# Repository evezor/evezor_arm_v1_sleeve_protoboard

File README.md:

# evezor_arm_v1_sleeve_protoboard

This board was intended to sit at the elbow of the robotic arm and serve as a prototyping area to create new ciruits. It has a 10 pin IDE port to connect gpio to the sleeve controller board, but this avenue was abandoned as there were many issues keeping things simple.

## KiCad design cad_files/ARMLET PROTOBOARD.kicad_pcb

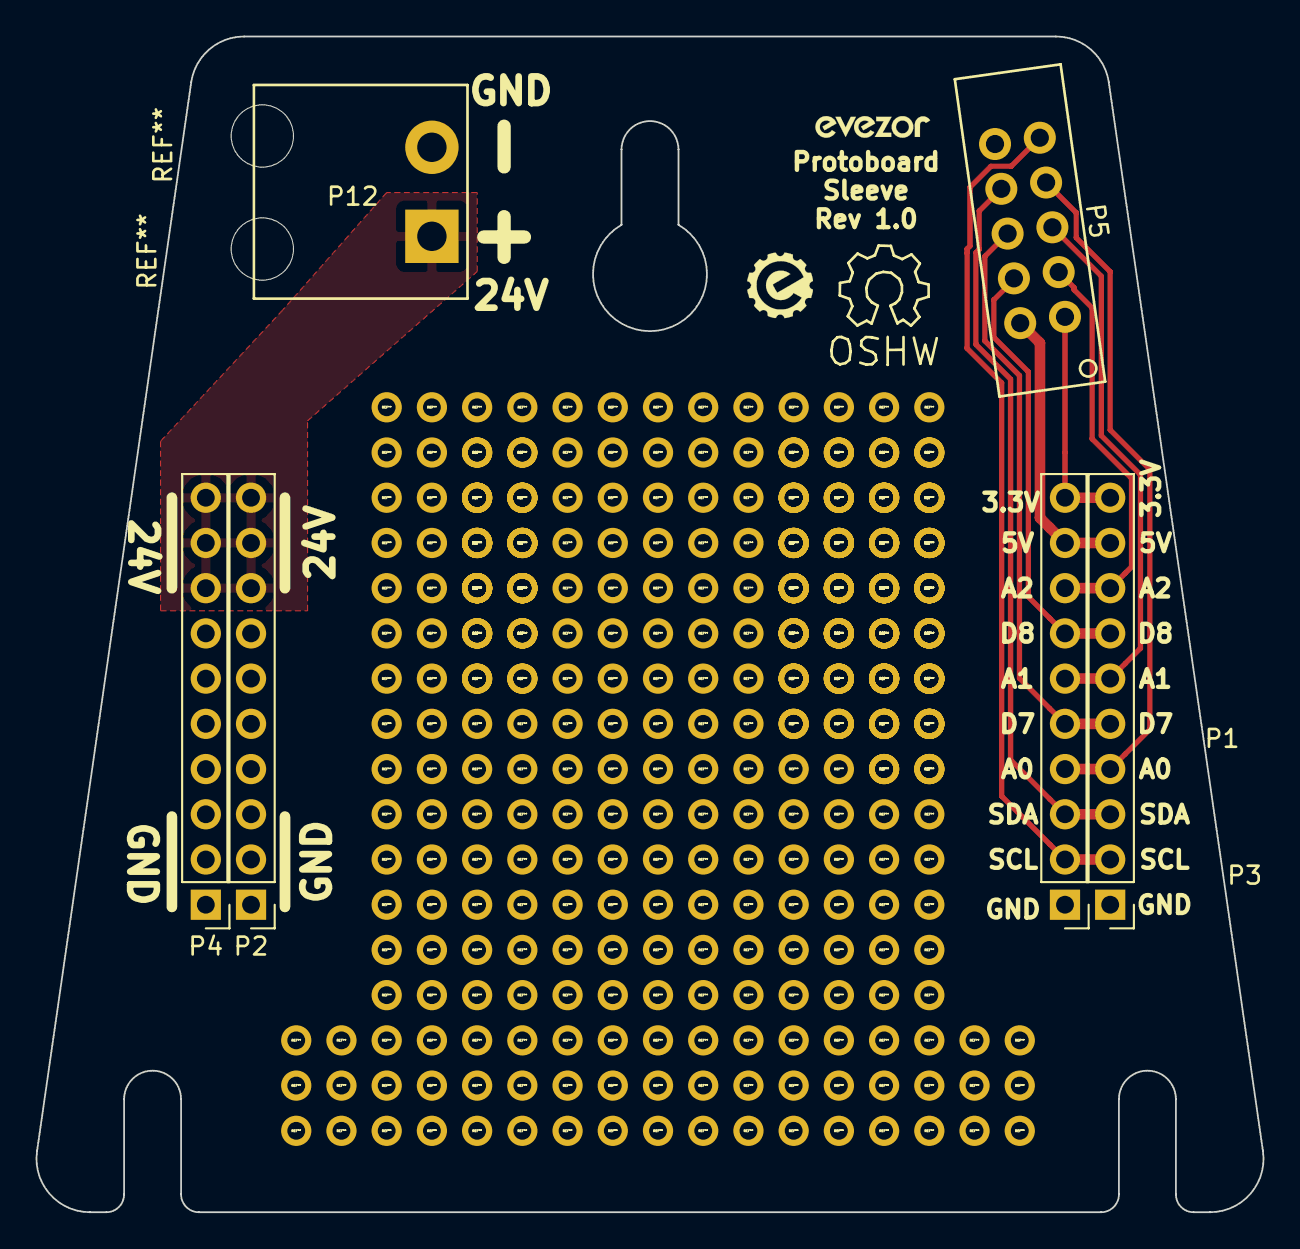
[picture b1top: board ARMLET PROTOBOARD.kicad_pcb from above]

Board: 2 copper layers, 68.9 x 66.0 mm, 6 parts (0 on the bottom side), 12 nets.

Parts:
P1, P2, P3, P4: CONN_01X10; Pin_Header_Straight_1x10_Pitch2.54mm
P5: CONN_02X05; RIBBON_TO_BOARD
P12: CONN_01X02; CONN_ON_SHORE_2x_15A

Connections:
24V_1: P2.8, P2.9, P2.10, P4.8, P4.9, P4.10, P12.2
+3V3: P1.10, P3.10, P5.1
+5V: P1.9, P3.9, P5.2
A0: P1.4, P3.4, P5.7
A1: P1.6, P3.6, P5.5
A2: P1.8, P3.8, P5.3
D7: P1.5, P3.5, P5.6
D8: P1.7, P3.7, P5.4
GND: P1.1, P3.1, P5.10
GNDPWR: P2.1, P2.2, P2.3, P4.1, P4.2, P4.3, P12.1
SCL: P1.2, P3.2, P5.9
SDA: P1.3, P3.3, P5.8

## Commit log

2023-09-20 Create LICENSE
2023-09-20 init
